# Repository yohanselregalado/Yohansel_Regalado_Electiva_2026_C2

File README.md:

# Yohansel_Regalado_Electiva_2026_C2

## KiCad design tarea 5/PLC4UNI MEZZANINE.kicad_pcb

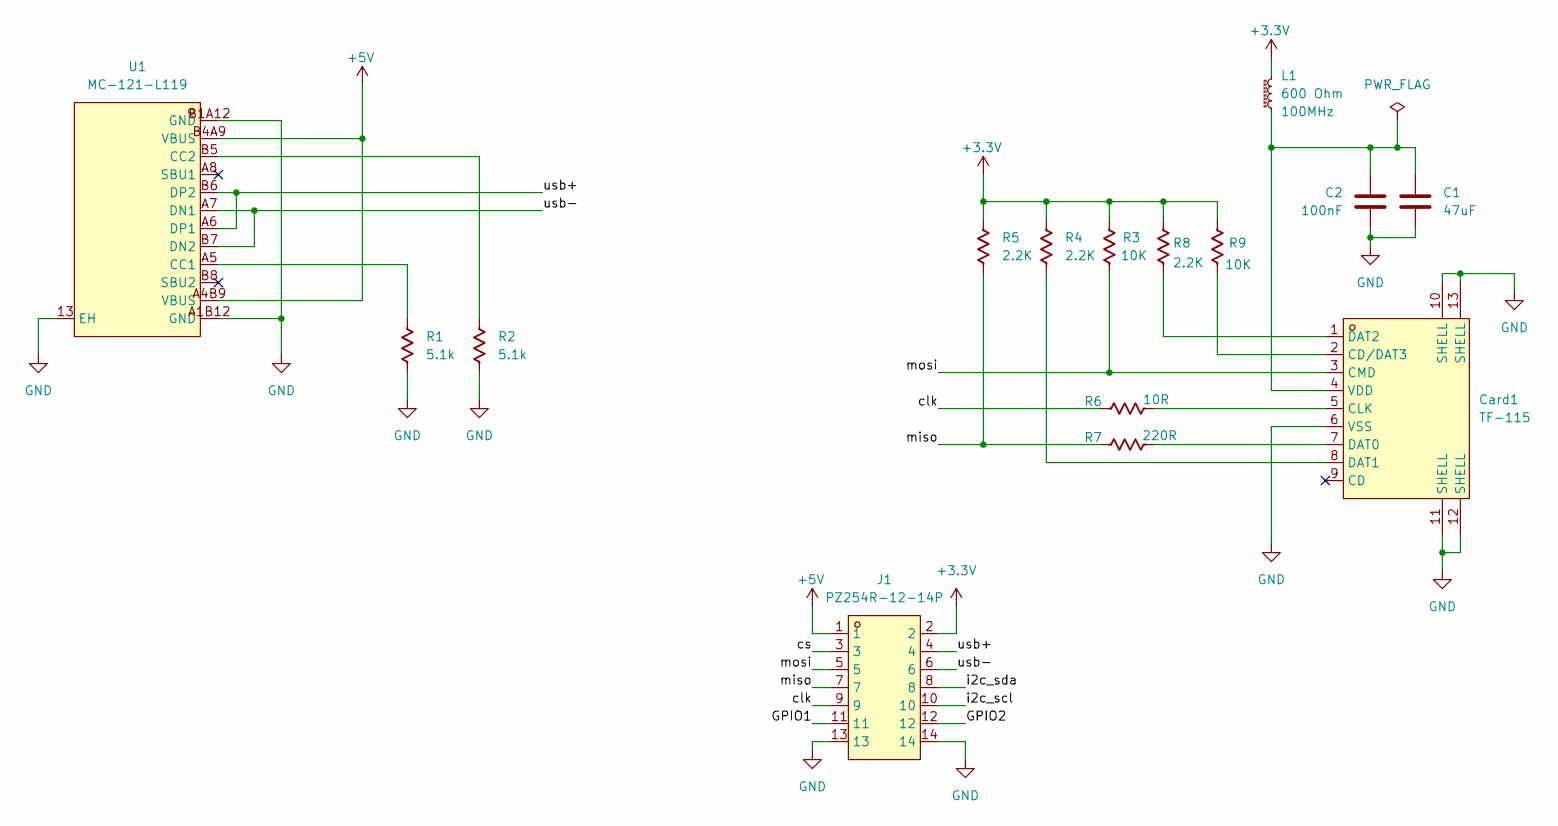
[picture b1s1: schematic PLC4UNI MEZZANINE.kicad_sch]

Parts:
C1: 47uF; C_0603_1608Metric
C2: 100nF; C_0603_1608Metric
Card1: TF-115; TF-SMD_TF-115; LCSC Part C266620
J1: PZ254R-12-14P; HDR-TH_14P-P2.54-H-M-R2-C7-S2.54; LCSC Part C492435
L1: 600 Ohm; C_0805_2012Metric
R1, R2: 5.1k; R_0603_1608Metric
R3, R9: 10K; R_0603_1608Metric
R4, R5, R8: 2.2K; R_0603_1608Metric
R6: 10R; R_0603_1608Metric
R7: 220R; R_0603_1608Metric
U1: MC-121-L119; USB-C-SMD_HANBO_MC-121-L119; LCSC Part C6332278

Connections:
+3.3V: J1.2, L1.2, R3.1, R4.1, R5.1, R8.1, R9.1
+5V: J1.1, U1.A4B9 (VBUS), U1.B4A9 (VBUS)
/GPIO1: J1.11
/GPIO2: J1.12
/clk: J1.9, R6.1
/cs: J1.3
/i2c_scl: J1.10
/i2c_sda: J1.8
/miso: J1.7, R5.2, R7.1
/mosi: Card1.3 (CMD), J1.5, R3.2
/usb+: J1.4, U1.A6 (DP1), U1.B6 (DP2)
/usb-: J1.6, U1.A7 (DN1), U1.B7 (DN2)
GND: C1.2, C2.2, Card1.6 (VSS), Card1.10 (SHELL), Card1.11 (SHELL), Card1.12 (SHELL), Card1.13 (SHELL), J1.13, J1.14, R1.2, R2.2, U1.13 (EH), U1.A1B12 (GND), U1.B1A12 (GND)
unnamed: Card1.2 (CD/DAT3), R9.2
unnamed: Card1.5 (CLK), R6.2
unnamed: Card1.7 (DAT0), R7.2
unnamed: Card1.8 (DAT1), R4.2
unnamed: Card1.1 (DAT2), R8.2
unnamed: C1.1, C2.1, Card1.4 (VDD), L1.1
unnamed: R1.1, U1.A5 (CC1)
unnamed: R2.1, U1.B5 (CC2)

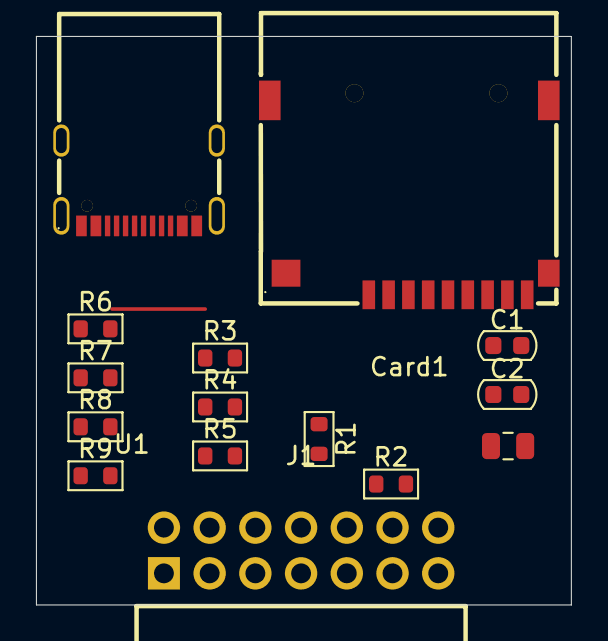
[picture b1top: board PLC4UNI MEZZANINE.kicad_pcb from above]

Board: 2 copper layers, 29.7 x 31.6 mm, 15 parts (0 on the bottom side), 16 nets.

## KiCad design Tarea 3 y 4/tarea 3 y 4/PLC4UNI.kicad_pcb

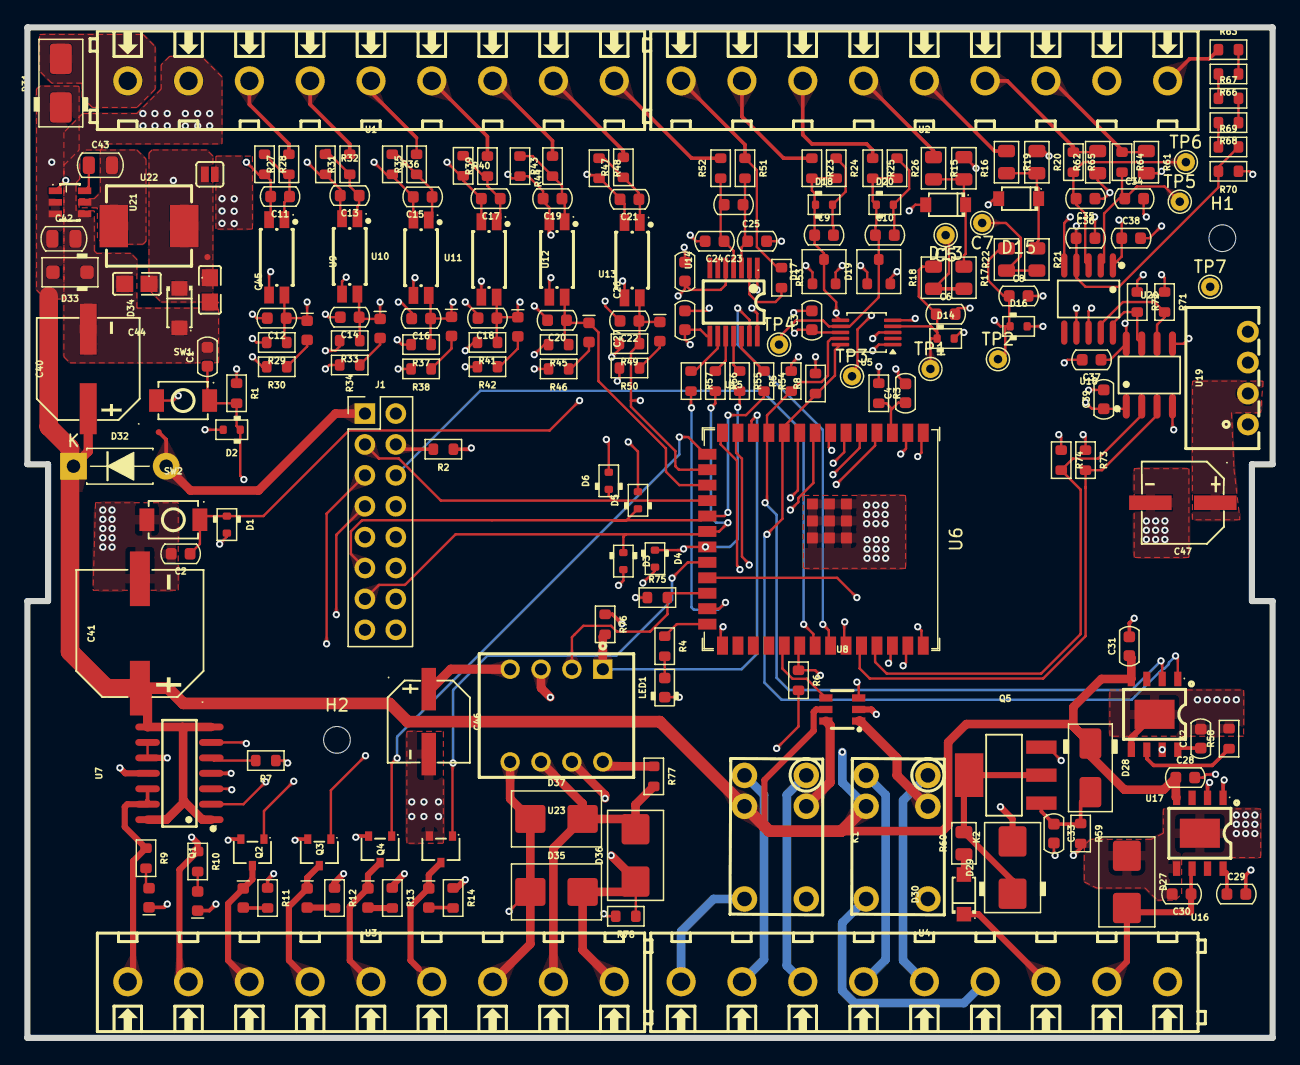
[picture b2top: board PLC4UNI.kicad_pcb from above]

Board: 4 copper layers, 102.4 x 83.1 mm, 209 parts (0 on the bottom side), 134 nets.

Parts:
C1, C2, C6, C8: 47pF; C_0603_1608Metric
C3, C9, C10, C23, C24, C25, C26, C27, C30, C37, C38, C39: 100nF; C_0603_1608Metric
C4, C28, C29, C33: 1uF; C_0603_1608Metric
C5, C7: 100nF; TestPoint_THTPad_D1.5mm_Drill0.7mm
C11, C12, C13, C14, C15, C16, C17, C18, C19, C20, C21, C22, C31, C32: C_0603; C_0603_1608Metric
C34, C35: 33nF; C_0603_1608Metric
C36: 68nF; C_0603_1608Metric
C40: 100uF/50V; CAP-SMD_BD8.0-L8.3-W8.3-FD
C41: 220uF/50V; CAP-SMD_BD10.0-L10.3-W10.3-LS11.3-FD
C42: 10uF/50V; C_0805_2012Metric
C43: 100nF; C_0805_2012Metric
C44, C45: 22uF/16V; C0805
C46, C47: 47uF/16V; CAP-SMD_BD6.3-L6.6-W6.6-FD
D1, D2, D3, D4, D5, D6: ESD5Z3.3T; D_SOD-523
D7, D8, D9, D10, D11, D12, D21, D22, D23, D24, D25, D26: Red; LED_0603_1608Metric_Red
D13, D15: 1N5819HW-7-F; SOD-123_L2.7-W1.6-LS3.7-RD
D14, D16, D18, D20: PESD5Z3.3; D_SOD-523
D17, D19: BAT54S; SOT-23
D27, D35, D36, D37: SMBJ12CA; D_SMB_TVS
D28: SMAJ12A; D_SMA
D29: SMBJ28A; D_SMB
D30: DSK120_C22466355; SOD-123FL_L2.7-W1.8-LS3.8-RD
D31: MBRA340T; D_SMA
D32: 1N5819; D_DO-41_SOD81_P7.62mm_Horizontal
D33: SMF24CA; D_SOD-123F
D34: SMF3.3; SOD-123FL_L3.0-W1.9-LS3.7-FD
H1, H2: MountingHole; MountingHole_2.2mm_M2_DIN965
J1: Conn_02x08_Odd_Even; PinHeader_2x08_P2.54mm_Vertical
JP1: Jumper_2_NO
K1, K2: G5V-1-DC3; RELAY-TH_G5V-1
LED1: LED_0603_Red; LED_0603_1608Metric
Q1, Q2, Q3, Q4: ZXMS6004FFQTA; SOT-23F_L2.9-W1.8-P0.95-LS2.4-BR
Q5: NCE60P04R; SOT-223-3_L6.5-W3.4-P2.30-LS7.0-BR
R1: 100k; R_0603_1608Metric
R2, R6, R7, R51, R52: 0R; R_0603_1608Metric
R3, R65, R77, R78: 1k; R_0603_1608Metric
R4: 2.2k; R_0603_1608Metric
R5, R8: 4.7k; R_0603_1608Metric
R9, R10, R11, R12, R13, R14, R58, R71, R72, R73, R74: R_0603; R_0603_1608Metric
R15, R19: 49.9R; R_0805_2012Metric
R16, R20: 120R; R_0805_2012Metric
R17, R18, R21, R22: R_0805; R_0805_2012Metric
R23, R25: 2.2K; R_0603_1608Metric
R24, R26: 1.05K; R_0603_1608Metric
R27, R31, R35, R39, R43, R47: 3.3K; R_0603_1608Metric
R28, R32, R36, R40, R44, R48: 3.6K; R_0603_1608Metric
R29, R33, R37, R41, R45, R49: 22K; R_0603_1608Metric
R30, R34, R38, R42, R46, R50: 220R; R_0603_1608Metric
R53: 20K; R_0603_1608Metric
R54, R55, R56, R57: 150R; R_0603_1608Metric
R59: 470K; R_0603_1608Metric
R60: 15R; R_0805_2012Metric
R61, R62: R51; R_0805_2012Metric
R63, R66, R67, R68, R69: 390k; R_0603_1608Metric
R64: 1K; R_0603_1608Metric
R70: 510; R_0603_1608Metric
R75, R76: 10k; R_0603_1608Metric
SW1, SW2: TS-1088-AR02016; SW-SMD_L3.9-W3.0-P4.45
TP1, TP2, TP3, TP4, TP5, TP6, TP7: TestPoint; TestPoint_THTPad_D1.5mm_Drill0.7mm
TP8, TP9, TP10: 0.5mm; TestPoint-0.5mm
U1, U2, U3, U4: ScrewTerminal1-1x9-P5.0mm; CONN-TH_9P-P5.00_DB127V-5.0-9P-GN-S
U5: ADS1115IDGS; TSSOP-10_3x3mm_P0.5mm
U6: ESP32-S3-WROOM-1; ESP32-S3-WROOM-1U
U7: BTS723GWXUMA1; SOIC-14_L8.7-W3.9-P1.27-LS6.0-BL
U8: LK1802; SOT-23-6_L2.9-W1.6-P0.95-LS2.8-BR
U9, U10, U11, U12, U13, U14: AT3H4B-CUH-S; SSOP-4_L2.7-W4.6-P1.27-LS7.0-TL
U15: MAX31856MUD+; TSSOP-14_L5.0-W4.4-P0.65-LS6.4-BL
U16: GP8211S-TC50-EW; ESOP-8_L4.9-W3.9-P1.27-LS6.0-BL-EP
U17: GP8302-TC50-EW; ESOP-8_L4.9-W3.9-P1.27-LS6.0-BL-EP
U18: BL0942; SSOP-10_L4.9-W3.9-P1.00-LS6.0-BL
U19: B0303S-1WR3_C7465185; PWRM-TH_BXXXXS-1WR3
U20: ISO7021DR; SOIC-8_L4.9-W3.9-P1.27-LS6.0-BL
U21: AP63203WU-7; TSOT-26_L2.9-W1.6-P0.95-LS2.8-BL
U22: APH0630T4R7M; IND-SMD_L7.0-W6.6_APH0630
U23: TD301M485_C5451847; COMM-TH_TD301M485

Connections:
3.3V: C3.1, C26.1, C27.1, C39.1, C46.1, C47.1, D17.2 (K), D19.2 (K), J1.2, JP1.2 (B), R1.1, R2.1, R3.1, R5.2, R8.2, R11.1, R12.1, R13.1, R14.1, R29.2, R30.2, R33.2, R34.2, R37.2, R38.2, R41.2, R42.2, R45.2, R46.2, R49.2, R50.2, R73.1, R74.1, R75.1, R76.1, U5.8 (VDD), U6.2 (3V3), U7.11 (SPU), U15.5 (AVDD), U15.8 (DVDD), U19.2 (+Vin), U20.1 (VCC1), U23.4 (VCC)
3.3V_P: C37.1, C38.1, R71.1, R72.1, TP7.1 (1_1), U18.1 (VDD), U18.8 (SCLK_BPS), U19.4 (+Vout), U20.8 (VCC2)
+5V: D32.2 (A), J1.1, TP8.1 (1_1)
+24V: D31.2 (A), U1.9
/plc4uni_top/CON-IN_CT_N: R62.2, R65.1, U2.4
/plc4uni_top/CON-IN_CT_P: R61.1, R64.1, U2.3
/plc4uni_top/CON_IN_0-10V_1: R23.1, U2.8
/plc4uni_top/CON_IN_0-10V_2: R25.1, U2.7
/plc4uni_top/CON_IN_4-20MA_1: R15.1, U2.6
/plc4uni_top/CON_IN_4-20MA_2: R19.1, U2.5
/plc4uni_top/CON_IN_NPN1: R27.2, U1.7
/plc4uni_top/CON_IN_NPN2: R31.2, U1.6
/plc4uni_top/CON_IN_NPN3: R35.2, U1.5
/plc4uni_top/CON_IN_NPN4: R39.2, U1.4
/plc4uni_top/CON_IN_PNP1: R43.2, U1.3
/plc4uni_top/CON_IN_PNP2: R47.2, U1.2
/plc4uni_top/CON_IN_TC+: R52.2, U1.1
/plc4uni_top/CON_IN_TC-: R51.1, R53.1, U2.9
/plc4uni_top/CON_IN_VAC-P: R63.1, U2.1
/plc4uni_top/CON_OUT_0-10V_1: C30.1, D27.2 (A), U4.8, U16.6 (VOUT)
/plc4uni_top/CON_OUT_4-20MA_1: D30.1, U4.7
/plc4uni_top/CON_OUT_NPN1: D9.1 (K), Q1.3 (D), U3.3
/plc4uni_top/CON_OUT_NPN2: D10.1 (K), Q2.3 (D), U3.4
/plc4uni_top/CON_OUT_NPN3: D11.1 (K), Q3.3 (D), U3.5
/plc4uni_top/CON_OUT_NPN4: D12.1 (K), Q4.3 (D), U3.6
/plc4uni_top/CON_OUT_PNP1: R9.1, U3.1, U7.12 (OUT1), U7.13 (OUT1)
/plc4uni_top/CON_OUT_PNP2: R10.1, U3.2, U7.9 (OUT2), U7.10 (OUT2)
/plc4uni_top/CON_OUT_RLY1-COM: K1.5, U4.1
/plc4uni_top/CON_OUT_RLY1-NC: K1.1, U4.2
/plc4uni_top/CON_OUT_RLY1-NO: K1.10, U4.3
/plc4uni_top/CON_OUT_RLY2-COM: K2.5, U4.6
/plc4uni_top/CON_OUT_RLY2-NC: K2.1, U4.4
/plc4uni_top/CON_OUT_RLY2-NO: K2.10, U4.5
/plc4uni_top/CON_RS485_A: D35.2 (A), D36.1 (K), R78.1, U3.9, U23.7 (B)
/plc4uni_top/CON_RS485_B: D36.2 (A), D37.2 (A), R77.2, U3.8, U23.6 (A)
/plc4uni_top/CON_RS485_G: D35.1 (K), D37.1 (K), R78.2, U3.7, U23.5 (RGND)
/plc4uni_top/EMRX: R73.2, U6.36 (U0RXD/GPIO44/CLK_OUT2), U20.3 (INB)
/plc4uni_top/EM_TX: R74.2, U6.37 (U0TXD/GPIO43/CLK_OUT1), U20.2 (OUTA)
/plc4uni_top/EN: C4.1, R3.2, U6.3 (EN)
/plc4uni_top/I2C_SCK: J1.10, R8.1, U5.10 (SCL), U6.10 (GPIO17/U1TXD/ADC2_CH6), U16.1 (SCLK), U17.1 (SLCK)
/plc4uni_top/I2C_SDA: J1.8, R5.1, U5.9 (SDA), U6.11 (GPIO18/U1RXD/ADC2_CH7/CLK_OUT3), U16.2 (SDA), U17.2 (SDA)
/plc4uni_top/IN-0-10V1/COM: C10.2, D20.2 (A), R26.1
/plc4uni_top/IN-0-10V1/OUT3V3: C10.1, D19.3 (C), D20.1 (K), R25.2, R26.2, TP4.1 (1_1), U5.7 (AIN3)
/plc4uni_top/IN-0-10V/COM: C9.2, D18.2 (A), R24.1
/plc4uni_top/IN-0-10V/OUT3V3: C9.1, D17.3 (C), D18.1 (K), R23.2, R24.2, TP3.1 (1_1), U5.6 (AIN2)
/plc4uni_top/IN-4-20MA1/OUT: C8.1, D16.1 (K), R22.2, TP2.1 (1_1), U5.5 (AIN1)
/plc4uni_top/IN-4-20MA/OUT: C6.1, D14.1 (K), R18.2, TP1.1 (1_1), U5.4 (AIN0)
/plc4uni_top/IN_NPN1: C12.1, D21.1 (K), R29.1, U6.4 (GPIO4/TOUCH4/ADC1_CH3), U9.4 (COL)
/plc4uni_top/IN_NPN2: C14.1, D22.1 (K), R33.1, U6.5 (GPIO5/TOUCH5/ADC1_CH4), U10.4 (COL)
/plc4uni_top/IN_NPN3: C16.1, D23.1 (K), R37.1, U6.6 (GPIO6/TOUCH6/ADC1_CH5), U11.4 (COL)
/plc4uni_top/IN_NPN4: C18.1, D24.1 (K), R41.1, U6.7 (GPIO7/TOUCH7/ADC1_CH6), U12.4 (COL)
/plc4uni_top/IN_PNP1: C20.1, D25.1 (K), R45.1, U6.17 (GPIO9/TOUCH9/ADC1_CH8/FSPIHD/SUBSPIHD), U13.4 (COL)
/plc4uni_top/IN_PNP2: C2.1, C22.1, D1.1 (K), D26.1 (K), R49.1, SW2.2, U6.16 (GPIO46), U14.4 (COL)
/plc4uni_top/LCD_CS: J1.7, U6.35 (MTMS/GPIO42)
/plc4uni_top/LCD_EN: J1.4, R2.2
/plc4uni_top/LED_INFO: R4.1, U6.26 (GPIO45)
/plc4uni_top/OUT-PNP/ST1: R6.2, U7.3 (ST1)
/plc4uni_top/OUT-PNP/ST2: R7.2, U7.5 (ST2)
/plc4uni_top/OUT_NPN1: Q1.1 (IN), U6.39 (GPIO1/TOUCH1/ADC1_CH0)
/plc4uni_top/OUT_NPN2: Q2.1 (IN), U6.38 (GPIO2/TOUCH2/ADC1_CH1)
/plc4uni_top/OUT_NPN3: Q3.1 (IN), U6.15 (GPIO3/TOUCH3/ADC1_CH2)
/plc4uni_top/OUT_NPN4: Q4.1 (IN), U6.22 (GPIO14/TOUCH14/ADC2_CH3/FSPIWP/FSPIDQS/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)
/plc4uni_top/OUT_PNP1: U6.8 (GPIO15/U0RTS/ADC2_CH4/XTAL_32K_P), U7.2 (IN1)
/plc4uni_top/OUT_PNP2: U6.9 (GPIO16/U0CTS/ADC2_CH5/XTAL_32K_N), U7.6 (IN2)
/plc4uni_top/OUT_RLY1: U6.23 (GPIO21), U8.3 (1B)
/plc4uni_top/OUT_RLY2: U6.31 (GPIO38/FSPIWP/SUBSPIWP), U8.4 (2B)
/plc4uni_top/RESET: C1.1, D2.1 (K), J1.5, R1.2, SW1.2, U6.27 (GPIO0/BOOT)
/plc4uni_top/RS485-RX: R76.2, U6.12 (GPIO8/TOUCH8/ADC1_CH7/SUBSPICS1), U23.1 (RXD)
/plc4uni_top/RS485-TX: R75.2, U6.24 (GPIO47/SPICLK_P/SUBSPICLK_P_DIFF), U23.2 (TXD)
/plc4uni_top/SD_CS: D6.1 (K), J1.3, U6.18 (GPIO10/TOUCH10/ADC1_CH9/FSPICS0/FSPIIO4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)
/plc4uni_top/SPI_CLK: D3.1 (K), J1.13, R56.2, U6.20 (GPIO12/TOUCH12/ADC2_CH1/FSPICLK/FSPIIO6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)
/plc4uni_top/SPI_MISO: D4.1 (K), J1.9, R55.2, U6.21 (GPIO13/TOUCH13/ADC2_CH2/FSPIQ/FSPIIO7/S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)
/plc4uni_top/SPI_MOSI: D5.1 (K), J1.11, R54.2, U6.19 (GPIO11/TOUCH11/ADC2_CH0/FSPID/FSPIIO5/S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)
/plc4uni_top/ST1_ST2: R6.1, R7.1, U6.32 (MTCK/GPIO39/CLK_OUT3/SUBSPICS1)
/plc4uni_top/TC_FAULT: U6.34 (MTDI/GPIO41/CLK_OUT1), U15.13 (~FAULT)
/plc4uni_top/TEMP_CS: R57.2, U6.25 (GPIO48/SPICLK_N/SUBSPICLK_N_DIFF)
/plc4uni_top/TP_INT: J1.6, U6.33 (MTDO/GPIO40/CLK_OUT2)
/plc4uni_top/USB+: J1.14, U6.14 (GPIO20/U1CTS/ADC2_CH9/CLK_OUT1/USB_D+)
/plc4uni_top/USB-: J1.12, U6.13 (GPIO19/U1RTS/ADC2_CH8/CLK_OUT2/USB_D-)
Earth: C34.2, C35.1, C36.2, C37.2, C38.2, R61.2, R62.1, R70.1, U2.2, U18.5 (GND), U18.7 (SEL), U19.3 (-Vout), U20.5 (GND2)
GND: C1.2, C2.2, C3.2, C4.2, C6.2, C8.2, C12.2, C14.2, C16.2, C18.2, C19.2, C20.2, C21.2, C22.2, C24.2, C25.2, C26.2, C27.2, C28.2, C29.2, C30.2, C31.2, C32.2, C33.2, C39.2, C40.2, C41.2, C42.2, C44.2, C45.2, C46.2, C47.2, D1.2 (A), D2.2 (A), D3.2 (A), D4.2 (A), D5.2 (A), D6.2 (A), D7.1 (K), D8.1 (K), D13.2, D14.2 (A), D15.2, D16.2 (A), D17.1 (A), D19.1 (A), D27.1 (K), D29.2 (A), D33.1 (K), D34.1, J1.15, J1.16, LED1.1 (K), Q1.2 (S), Q2.2 (S), Q3.2 (S), Q4.2 (S), R16.1, R20.1, R44.2, R48.2, R58.2, R59.2, SW1.1, SW2.1, U1.8, U4.9, U5.1 (ADDR), U5.3 (GND), U6.1 (GND), U6.40 (GND), U6.41 (GND), U7.4 (GND), U8.2 (E), U9.3 (EM), U10.3 (EM), U11.3 (EM), U12.3 (EM), U13.2 (CAT/AN), U13.3 (EM), U14.2 (CAT/AN), U14.3 (EM), U15.1 (AGND), U15.14 (DGND), U16.5 (GND), U16.9 (EP), U17.5 (GND), U17.9 (EP), U19.1 (-Vin), U20.4 (GND1), U21.4 (GND), U23.3 (GND)
unnamed: C5.1, R17.2, R18.1
unnamed: C7.1, R21.2, R22.1
unnamed: D7.2 (A), R9.2
unnamed: D8.2 (A), R10.2
unnamed: D9.2 (A), R11.2
unnamed: D10.2 (A), R12.2
unnamed: D11.2 (A), R13.2
unnamed: D12.2 (A), R14.2
unnamed: D13.1, R15.2, R16.2, R17.1
unnamed: D15.1, R19.2, R20.2, R21.1
unnamed: D21.2 (A), R30.1
unnamed: D22.2 (A), R34.1
unnamed: D23.2 (A), R38.1
unnamed: D24.2 (A), R42.1
unnamed: D25.2 (A), R46.1
unnamed: D26.2 (A), R50.1
unnamed: C33.1, D28.2 (A), Q5.1 (G), R59.1
unnamed: D29.1 (K), Q5.2 (D), Q5.4 (D), R60.2
unnamed: D30.2, R60.1
unnamed: C44.1, C45.1, D34.2, JP1.1 (A), TP10.1 (1_1), U21.1 (FB), U22.2
unnamed: LED1.2 (A), R4.2
unnamed: Q5.3 (S), U17.7 (IOUT)
unnamed: R63.2, R66.1
unnamed: R66.2, R67.1
unnamed: R67.2, R68.1
unnamed: R68.2, R69.1
unnamed: K2.9, U8.1 (1C)
unnamed: K1.9, U8.6 (2C)
unnamed: C11.1, R27.1, R28.1, U9.1 (AN/CAT)
unnamed: C13.1, R31.1, R32.1, U10.1 (AN/CAT)
unnamed: C15.1, R35.1, R36.1, U11.1 (AN/CAT)
unnamed: C17.1, R39.1, R40.1, U12.1 (AN/CAT)
unnamed: C19.1, R43.1, R44.1, U13.1 (AN/CAT)
unnamed: C21.1, R47.1, R48.1, U14.1 (AN/CAT)
unnamed: R53.2, U15.2 (BIAS)
unnamed: R56.1, U15.10 (SCK)
unnamed: R54.1, U15.12 (SDI)
unnamed: R55.1, U15.11 (SDO)
unnamed: C23.2, C24.1, R52.1, U15.4 (T+)
unnamed: C23.1, C25.1, R51.2, U15.3 (T-)
unnamed: R57.1, U15.9 (~CS)
unnamed: C29.1, U16.8 (V5V)
unnamed: R58.1, U17.6 (SET)
unnamed: C32.1, U17.8 (V5V)
unnamed: C35.2, R65.2, TP6.1 (1_1), U18.3 (IN)
unnamed: C34.1, R64.2, TP5.1 (1_1), U18.2 (IP)
unnamed: R71.2, U18.9 (RX/SDI), U20.6 (OUTB)
unnamed: R72.2, U18.10 (TX/SDO), U20.7 (INA)
unnamed: C36.1, R69.2, R70.2, U18.4 (VP)
unnamed: C43.1, U21.6 (BST)
unnamed: C43.2, U21.5 (SW), U22.1
unnamed: R77.1, U23.8 (VO)
VCC: C11.2, C13.2, C15.2, C17.2, C28.1, C31.1, C40.1, C41.1, C42.1, D28.1 (K), D31.1 (K), D32.1 (K), D33.2 (A), K1.2, K2.2, R28.2, R32.2, R36.2, R40.2, TP9.1 (1_1), U7.1 (VBB), U7.7 (VBB), U7.8 (VBB), U7.14 (VBB), U8.5 (COM), U9.2 (CAT/AN), U10.2 (CAT/AN), U11.2 (CAT/AN), U12.2 (CAT/AN), U16.4 (VCC), U17.4 (VCC), U21.2 (EN), U21.3 (VIN)

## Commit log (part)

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2026-06-11 Tarea 2
